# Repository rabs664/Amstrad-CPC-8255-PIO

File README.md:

# Amstrad CPC 8255 PIO
Simple 8255 PIO board compatible with the Amstrad CPC and MX4 connector.

## Objective
Prototyping board to Learn about the 8255 PIO, and how to write Z80 assembly using an Amstrad CPC.

## Background
Part of a number of modular cards using Z80 associated peripherals and the Amstrad CPC.

## Backplane
[CPC Amstrad Expansion Backplane by revaldinho](https://github.com/revaldinho/cpc_ram_expansion/wiki/CPC-Expansion-Backplane)

## IO Addressing
The IO Address can be selected using two sets of jumpers (CS_HB and CS_LB), supporting the following base address.

* F8E0 and F8F0
* F9E0 and F9F0
* FAE0 and FAF0
* FBE0 and FBF0

See [CPC Wiki IO Port Summary](https://www.cpcwiki.eu/index.php/I/O_Port_Summary) for a list of known IO ports used on the Amstrad CPC.

## Testing
The 8255 PIO board has been built and has been tested on an Amstrad CPC 6128.

## PCBs
PCBs are available from [Seeed Studio V2.0](https://www.seeedstudio.com/Amstrad-CPC-8255-PIO-g-1393845) or [Seeed Studio V3.1](https://www.seeedstudio.com/Simple-8255-PIO-board-compatible-with-the-Amstrad-CPC-and-MX4-connector-V3--g-1396645)

## Components
This [Digi-Key List](https://www.digikey.co.uk/en/mylists/list/ZWWIHRPLO7 ) contains all components excluding the 8255 which was purchased from EBay.

Note the right angled header for the port connections was not available at the time of producing this list but all other components were in stock for shipping immediately.

## Assembler
[RASM](https://github.com/EdouardBERGE/rasm)

## Resources
[CPCWiki](https://www.cpcwiki.eu/index.php/Main_Page)

Z80 Application by James W Coffron ISBN 0-89588-094-6

## Acknowledgements
[@revaldinho](https://github.com/revaldinho)

Don Prefontaine 

Peter Murray

[@EdouardBERGE](https://github.com/EdouardBERGE)

# Release History
## Version 2.0
* First Release
## Version 3.1
* KiCad created version of PCB.

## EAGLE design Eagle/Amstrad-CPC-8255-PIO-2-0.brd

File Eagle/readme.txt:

This folder contains files associated with the use of Eagle to create the schematics and PCB.

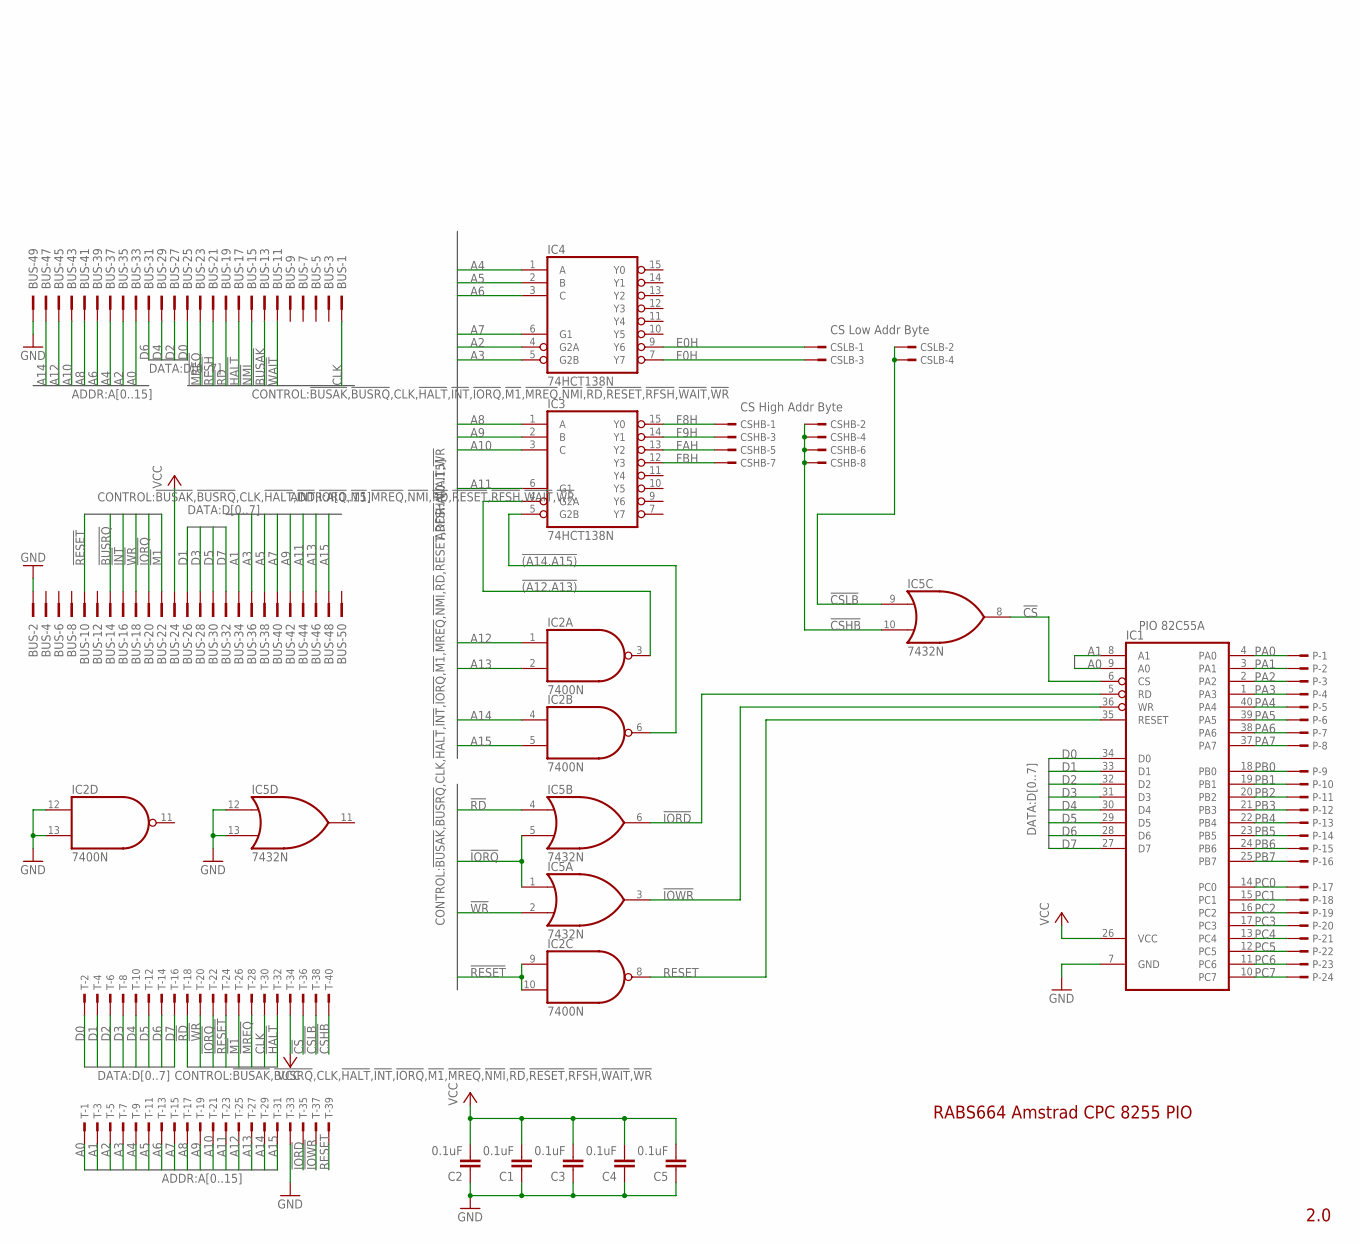
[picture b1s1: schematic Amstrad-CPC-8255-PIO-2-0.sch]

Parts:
BUS: 2550-; PAK100/2500-50
C1, C2, C3, C4, C5: 0.1uF; C050-025X075
CSHB: TSW-104-07-G-D; TSW-104-XX-G-D
CSLB: TSW-102-07-G-D; TSW-102-XX-G-D
IC1: 82C55A; DIL40
IC2: 7400N; DIL14
IC3, IC4: 74HCT138N; DIL16
IC5: 7432N; DIL14
P: TSW-124-07-G-S; TSW-124-XX-G-S
T: TSW-120-07-G-D; TSW-120-XX-G-D

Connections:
!(A12.A13): IC2.3 (O), IC3.4 (G2A)
!(A14.A15): IC2.6 (O), IC3.5 (G2B)
!BUSAK: BUS.13
!BUSRQ: BUS.14
!CS: IC1.6 (CS), IC5.8 (O), T.36
!CSHB: CSHB.2, CSHB.4, CSHB.6, CSHB.8, IC5.10 (I1), T.40
!CSLB: CSLB.2, CSLB.4, IC5.9 (I0), T.38
!HALT: BUS.17, T.32
!INT: BUS.16
!IORD: IC1.5 (RD), IC5.6 (O), T.35
!IORQ: BUS.20, IC5.1 (I0), IC5.5 (I1), T.22
!IOWR: IC1.36 (WR), IC5.3 (O), T.37
!M1: BUS.22, T.26
!MREQ: BUS.23, T.28
!NMI: BUS.15
!RD: BUS.19, IC5.4 (I0), T.18
!RESET: BUS.10, IC2.9 (I0), IC2.10 (I1), T.24
!RFSH: BUS.21
!WAIT: BUS.11
!WR: BUS.18, IC5.2 (I1), T.20
A0: BUS.33, IC1.9 (A0), T.1
A1: BUS.34, IC1.8 (A1), T.3
A2: BUS.35, IC4.4 (G2A), T.5
A3: BUS.36, IC4.5 (G2B), T.7
A4: BUS.37, IC4.1 (A), T.9
A5: BUS.38, IC4.2 (B), T.11
A6: BUS.39, IC4.3 (C), T.13
A7: BUS.40, IC4.6 (G1), T.15
A8: BUS.41, IC3.1 (A), T.17
A9: BUS.42, IC3.2 (B), T.19
A10: BUS.43, IC3.3 (C), T.21
A11: BUS.44, IC3.6 (G1), T.23
A12: BUS.45, IC2.1 (I0), T.25
A13: BUS.46, IC2.2 (I1), T.27
A14: BUS.47, IC2.4 (I0), T.29
A15: BUS.48, IC2.5 (I1), T.31
CLK: BUS.1, T.30
D0: BUS.25, IC1.34 (D0), T.2
D1: BUS.26, IC1.33 (D1), T.4
D2: BUS.27, IC1.32 (D2), T.6
D3: BUS.28, IC1.31 (D3), T.8
D4: BUS.29, IC1.30 (D4), T.10
D5: BUS.30, IC1.29 (D5), T.12
D6: BUS.31, IC1.28 (D6), T.14
D7: BUS.32, IC1.27 (D7), T.16
E0H: CSLB.1, IC4.9 (Y6)
F0H: CSLB.3, IC4.7 (Y7)
F8H: CSHB.1, IC3.15 (Y0)
F9H: CSHB.3, IC3.14 (Y1)
FAH: CSHB.5, IC3.13 (Y2)
FBH: CSHB.7, IC3.12 (Y3)
GND: BUS.2, BUS.49, C1.1, C2.1, C3.1, C4.1, C5.1, IC1.7 (GND), IC2.7 (GND), IC2.12 (I0), IC2.13 (I1), IC3.8 (GND), IC4.8 (GND), IC5.7 (GND), IC5.12 (I0), IC5.13 (I1), T.33
PA0: IC1.4 (PA0), P.1
PA1: IC1.3 (PA1), P.2
PA2: IC1.2 (PA2), P.3
PA3: IC1.1 (PA3), P.4
PA4: IC1.40 (PA4), P.5
PA5: IC1.39 (PA5), P.6
PA6: IC1.38 (PA6), P.7
PA7: IC1.37 (PA7), P.8
PB0: IC1.18 (PB0), P.9
PB1: IC1.19 (PB1), P.10
PB2: IC1.20 (PB2), P.11
PB3: IC1.21 (PB3), P.12
PB4: IC1.22 (PB4), P.13
PB5: IC1.23 (PB5), P.14
PB6: IC1.24 (PB6), P.15
PB7: IC1.25 (PB7), P.16
PC0: IC1.14 (PC0), P.17
PC1: IC1.15 (PC1), P.18
PC2: IC1.16 (PC2), P.19
PC3: IC1.17 (PC3), P.20
PC4: IC1.13 (PC4), P.21
PC5: IC1.12 (PC5), P.22
PC6: IC1.11 (PC6), P.23
PC7: IC1.10 (PC7), P.24
RESET: IC1.35 (RESET), IC2.8 (O), T.39
VCC: BUS.24, C1.2, C2.2, C3.2, C4.2, C5.2, IC1.26 (VCC), IC2.14 (VCC), IC3.16 (VCC), IC4.16 (VCC), IC5.14 (VCC), T.34

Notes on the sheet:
2.0
RABS664 Amstrad CPC 8255 PIO
PIO 82C55A
CS High Addr Byte
CS Low Addr Byte

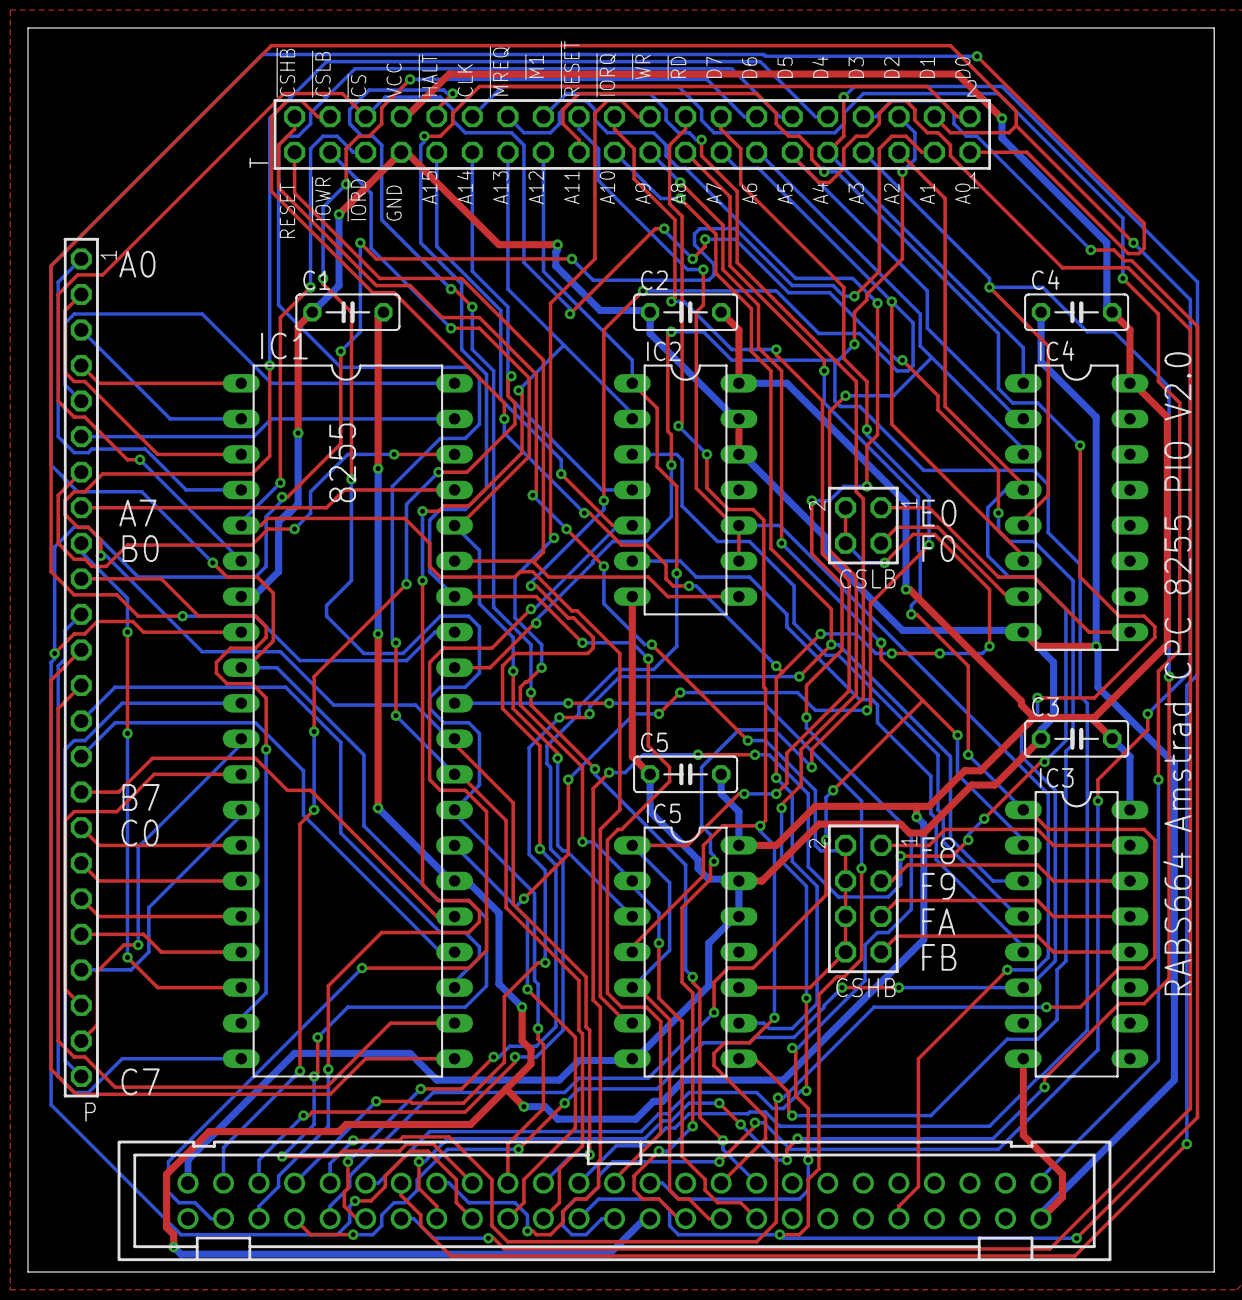
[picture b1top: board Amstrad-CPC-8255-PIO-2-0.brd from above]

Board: 2 copper layers, 84.8 x 88.9 mm, 15 parts (0 on the bottom side), 72 nets.

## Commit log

2023-05-28 Update README.md
    First update
2023-05-28 Create readme.txt
    folder readme description.
2023-05-28 Add files via upload
    First Release, changed name of files from Z80 PIO to 8255 PIO.
2023-05-28 Create Software-Files
2023-06-17 Update README.md
    Typo
2023-06-17 Update readme.txt
    Typo
2023-06-24 Changed to use RASM
2023-08-25 Update README.md
    Updated Seeed Studio References for PCBs
2024-01-26 Uploaded KiCad 7.0 schematic for version 3.1
    Noted that there was not a jpg image for version 3.1 board which was created in KiCad 7.0
2024-01-26 Added BOM from KiCAD 7.0 for version 3.1
    Noted that BOM only existed for version 2.0
2024-01-27 Pictures of Test Breaboard and v3.1
    Some picture of the test breadboard used and when connected to the V3.1 PIO board.
2024-01-27 Correct Logic Family for 74 245 ICs to use HCT.
2024-01-27 Delete Images/Amstrad-CPC-2855-PIO-Test-1-0.png
    Replaced by Amstrad-CPC-8255-PIO-Test-1-1.png with a correct to the logic family using HCT.
2025-07-20 Update README.md
    Removed invalid URL links
